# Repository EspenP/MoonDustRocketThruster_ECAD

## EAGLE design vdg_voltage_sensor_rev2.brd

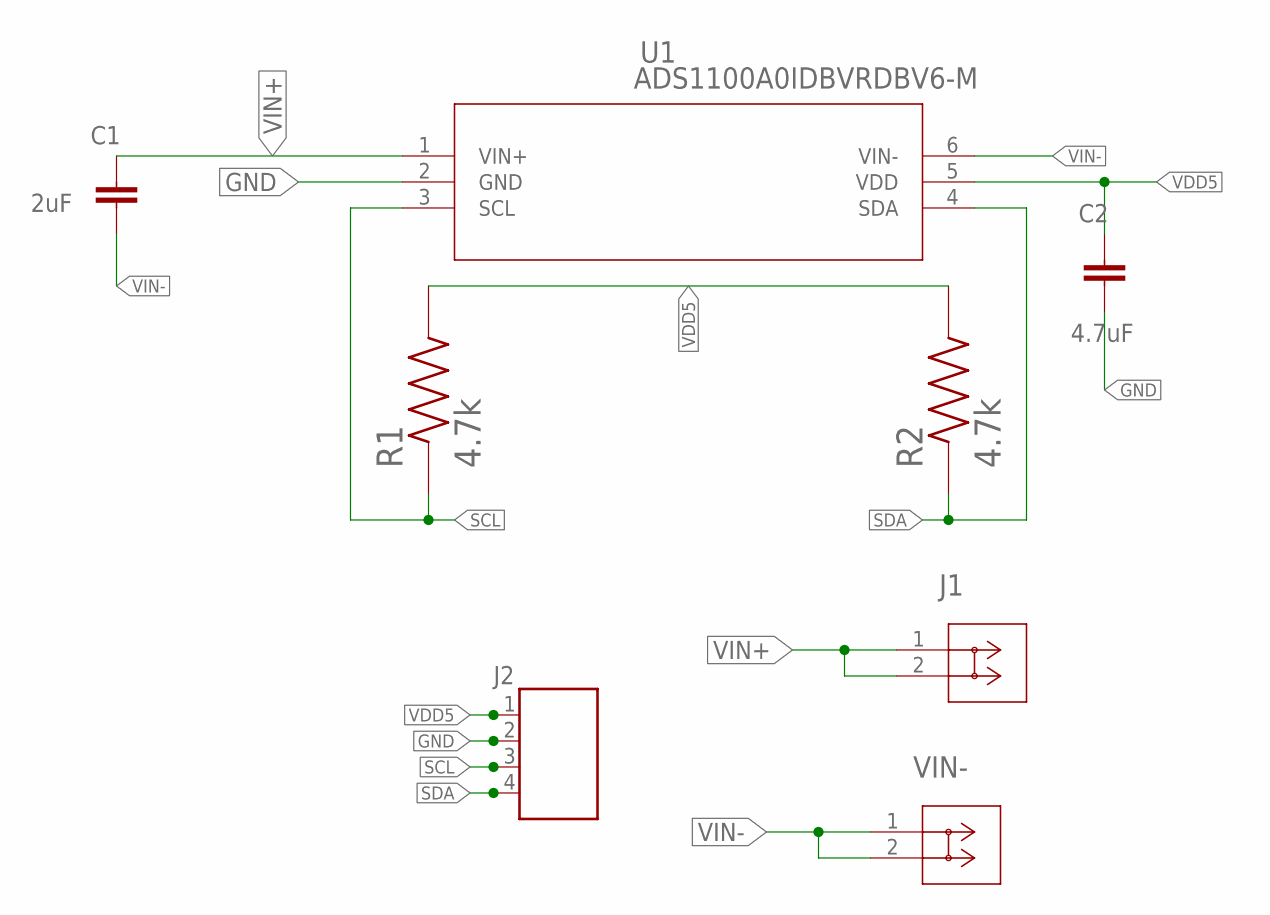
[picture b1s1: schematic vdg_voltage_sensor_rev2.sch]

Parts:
C1: 2uF; CAP_1206
C2: 4.7uF; CAP_1206
J1: VANDEGRAAFF; SR99S01VBNN00G7_MZC
J2: 691131710004
R1, R2: 4.7k; RESC3115X65N
U1: ADS1100A0IDBVRDBV6-M; DBV6-M
VIN-: SR99S01VBNN00G7; SR99S01VBNN00G7_MZC

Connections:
GND: C2.2, J2.2, U1.2 (GND)
SCL: J2.3, R1.1, U1.3 (SCL)
SDA: J2.4, R2.1, U1.4 (SDA)
VDD5: C2.1, J2.1, R1.2, R2.2, U1.5 (VDD)
VIN+: C1.1, J1.1, J1.2, U1.1 (VIN+)
VIN-: C1.2, U1.6 (VIN-), VIN-.1, VIN-.2

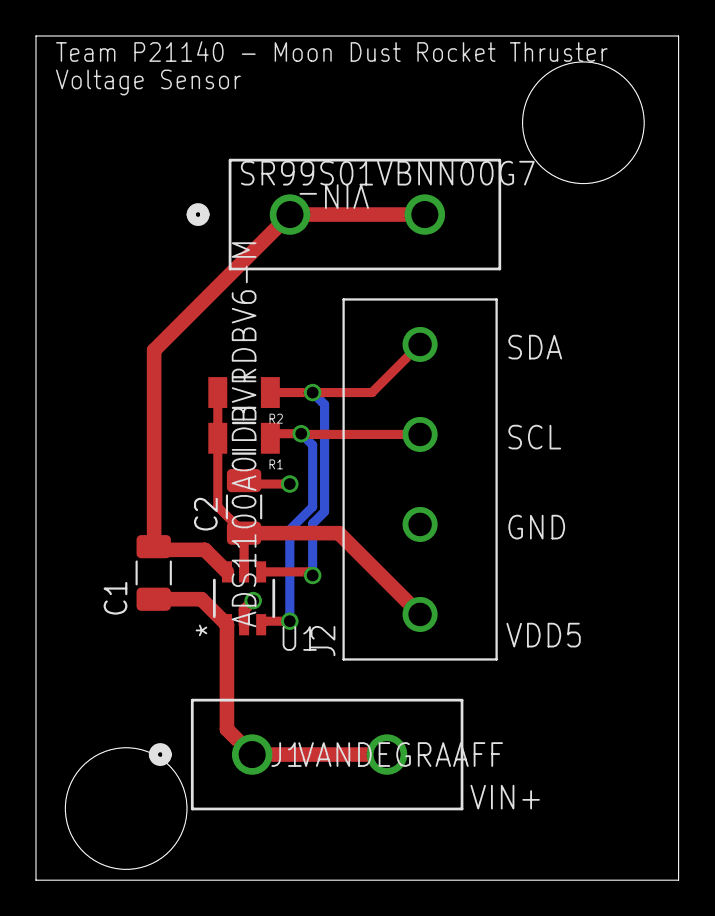
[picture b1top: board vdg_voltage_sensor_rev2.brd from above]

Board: 2 copper layers, 35.7 x 46.9 mm, 8 parts (0 on the bottom side), 6 nets.

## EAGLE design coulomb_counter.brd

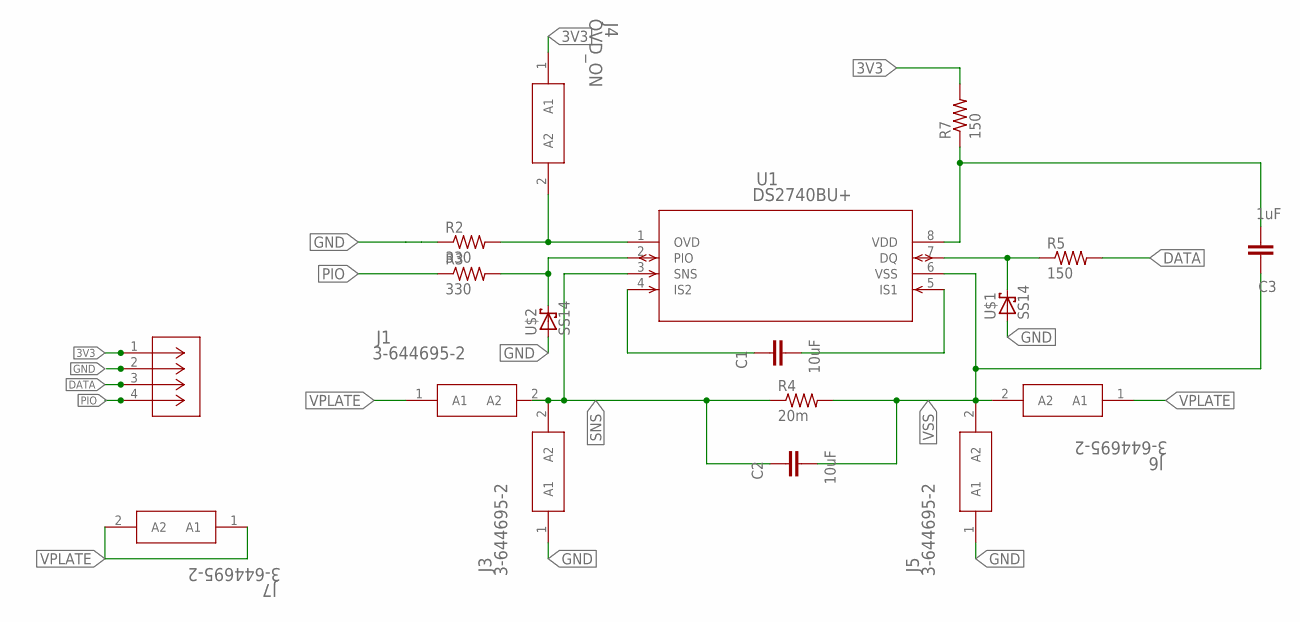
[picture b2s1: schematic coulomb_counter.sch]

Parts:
C1, C2: 10uF; CAP_1206
C3: 1uF; CAP_1206
J1, J3, J5, J6, J7: 3-644695-2; 3-644695-2_TYC
J2: 1935187; CONN_1935187_PXC
J4: OVD_ON; 3-644695-2_TYC
R2, R3: 330; RES_1206
R4: 20m; RES_1206
R5, R7: 150; RES_1206
U1: DS2740BU+; 21-0036K_MXM
U$1, U$2: SS14; DO-214AC

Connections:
3V3: J2.1, J4.1 (A1), R7.2
DATA: J2.3, R5.2
GND: J2.2, J3.1 (A1), J5.1 (A1), R2.1, U$1.A, U$2.A
unnamed: C3.2, R7.1, U1.8 (VDD)
unnamed: C1.2, U1.5 (IS1)
unnamed: C1.1, U1.4 (IS2)
unnamed: R3.2, U1.2 (PIO), U$2.C
unnamed: R5.1, U1.7 (DQ), U$1.C
OVD: J4.2 (A2), R2.2, U1.1 (OVD)
PIO: J2.4, R3.1
SNS: C2.1, J1.2 (A2), J3.2 (A2), R4.1, U1.3 (SNS)
VPLATE: J1.1 (A1), J6.1 (A1), J7.1 (A1), J7.2 (A2)
VSS: C2.2, C3.1, J5.2 (A2), J6.2 (A2), R4.2, U1.6 (VSS)

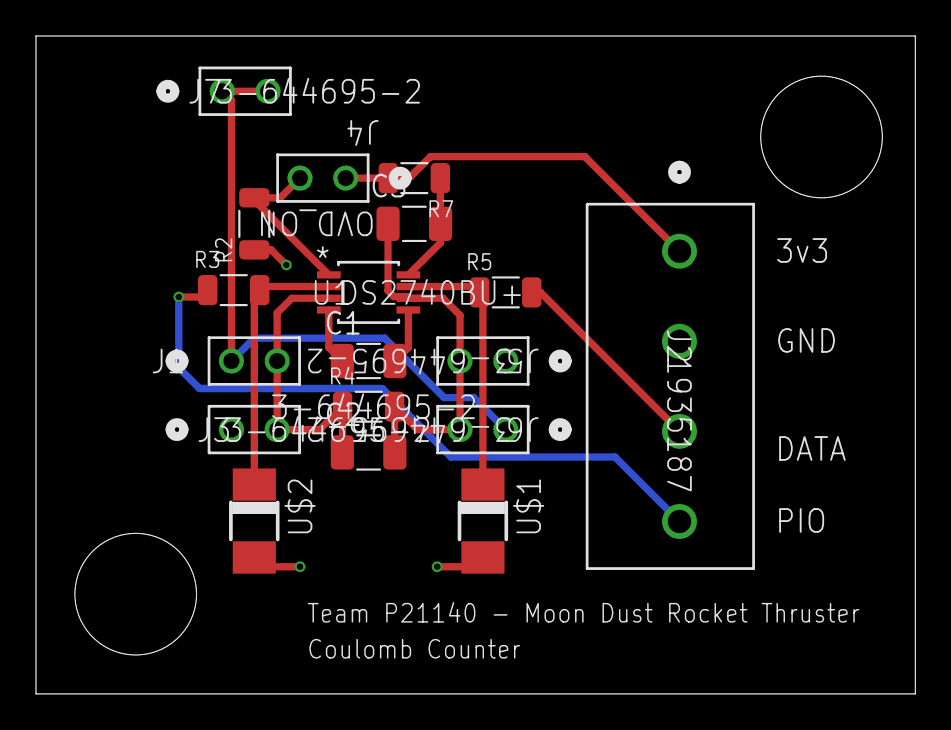
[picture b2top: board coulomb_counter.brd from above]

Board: 2 copper layers, 48.9 x 36.5 mm, 18 parts (0 on the bottom side), 13 nets.

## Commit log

2021-02-16 remove old png
    removed old png of old draft of voltage sensor
2021-02-21 Added full wiring diagram
    Added full wiring diagram and an image.
2021-03-04 Moved pictures into their own folder. Added pictures for both of the boards.

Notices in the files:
parts and their libraries:
COPYRIGHT: Copyright (C) 2018 Accelerated Designs. All rights reserved
Wurth_Elektronik_Electromechanic_Termina: Copyright: Würth Elektronik
